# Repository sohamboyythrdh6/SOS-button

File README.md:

# SOS-button
it's a button which can send your live location in emergency . its a really useful project which made from two microcontroler 
and it use a button to send your live location by asking help to your saved num.

this is really useful for those teenager studients who don't carry any smart phone or any other stuff so that they can make contact with parents . by just one click it can send your live location and your parents can alert that you need help.to make this project a xiaoesp32 which is basically the main brain of this project and for long range connectionsi use a A9G Core Board Module GPRS+GSM Development Board and for power the whole board i use a lipo battery with a tp4056 charging module to charge the battery.

<summary>📦 Bill of Materials (BOM)</summary>

| Component | Purpose | Qty | Cost (USD) | Distributor |
|-----------|---------|-----|------------|-------------|
| A9G Core Board Module (GPRS + GSM) | Main core of the project | 1 | $21.00 | Robu.in |
| Seeed Studio XIAO ESP32S3 | Secondary controller / processing unit | 1 | $11.00 | Robu.in |
| HT7333-A 3.3V LDO Regulator | Regulates the voltage to 3.3V | 1 | $1.00 | Robu.in |
| Tactile Push Button Switch | Sends the SOS signal | 1 | $2.00 | Robu.in |
| 3.7V 1250mAh 1S LiPo Battery | Powers the project | 1 | $5.00 | Robu.in |
| Lithium Battery Charger Module | Charges the LiPo battery | 1 | $1.00 | Robu.in |
| Slide Switch | Power ON/OFF control | 1 | $1.00 | Robu.in |

**Total Estimated Cost:** **$42.00 USD**

to build this project you need all the components and the pcb after that you can solder all those components and then upload the code during it you need to put your num at line 11.thats it you are done now within just oneclick a message and a call will send to your saved num

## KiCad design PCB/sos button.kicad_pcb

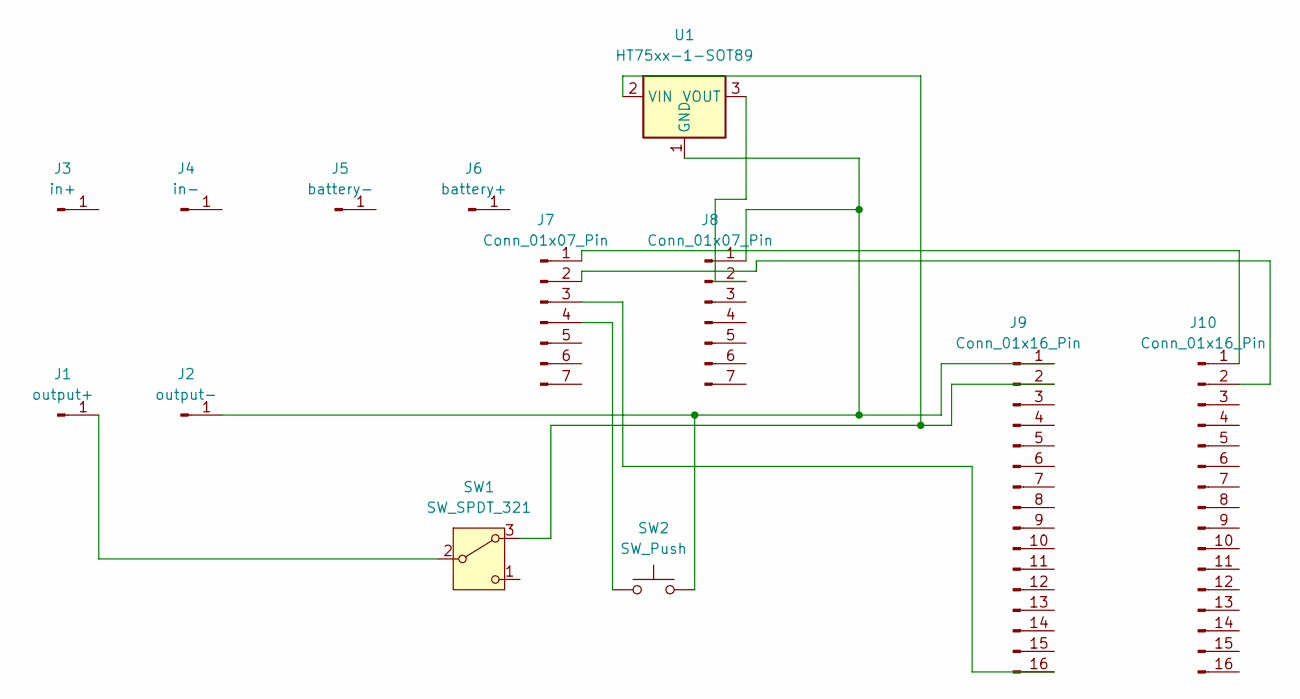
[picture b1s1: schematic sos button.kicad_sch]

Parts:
J1: output+; PinHeader_1x01_P1.00mm_Vertical
J2: output-; PinHeader_1x01_P1.00mm_Vertical
J3: in+; PinHeader_1x01_P1.00mm_Vertical
J4: in-; PinHeader_1x01_P1.00mm_Vertical
J5: battery-; PinHeader_1x01_P1.00mm_Vertical
J6: battery+; PinHeader_1x01_P1.00mm_Vertical
J7, J8: Conn_01x07_Pin; PinHeader_1x07_P1.00mm_Vertical
J9, J10: Conn_01x16_Pin; PinHeader_1x16_P1.00mm_Vertical
SW1: SW_SPDT_321; SW_SPDT_PCM12
SW2: SW_Push; SW_Push_1P1T_NO_CK_PTS125Sx43PSMTR
U1: HT75xx-1-SOT89; SOT-89-3

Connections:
unnamed: J1.1 (Pin_1_1), SW1.2 (B)
unnamed: J2.1 (Pin_1_1), J8.1, J9.1, SW2.2, U1.1 (GND)
unnamed: J7.3, J9.16
unnamed: J7.4, SW2.1
unnamed: J8.2, U1.3 (VOUT)
unnamed: J9.2, SW1.3 (A), U1.2 (VIN)
unnamed: J7.1, J10.1
unnamed: J7.2, J10.2

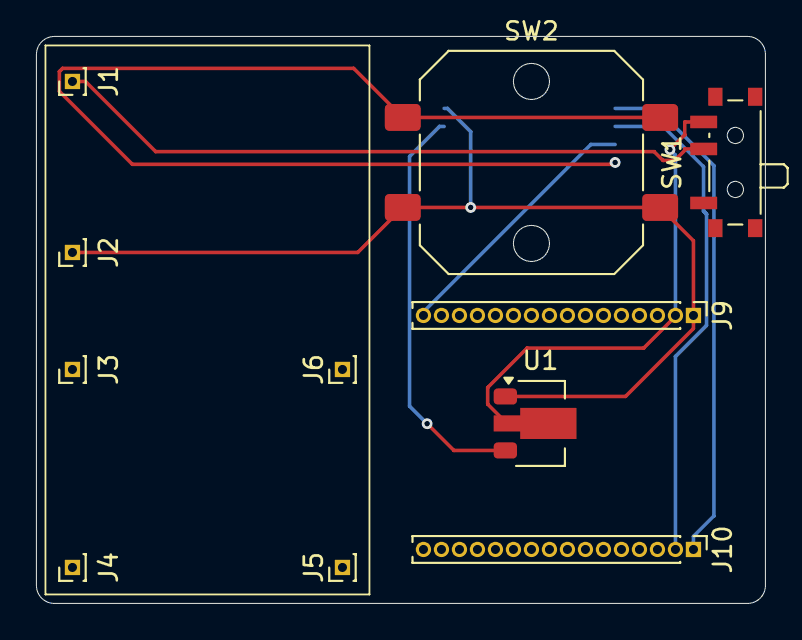
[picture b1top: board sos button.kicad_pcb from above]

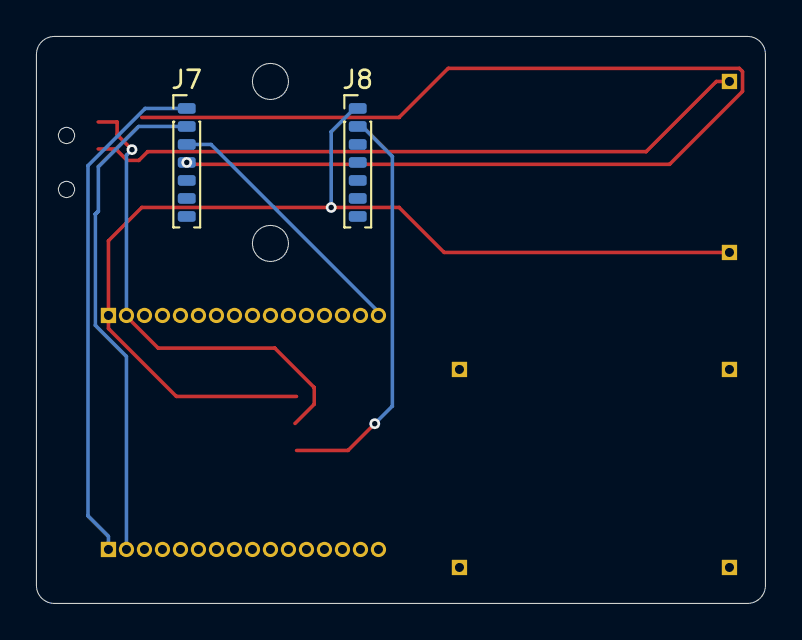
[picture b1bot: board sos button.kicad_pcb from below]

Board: 2 copper layers, 40.5 x 31.5 mm, 13 parts (2 on the bottom side), 8 nets.
